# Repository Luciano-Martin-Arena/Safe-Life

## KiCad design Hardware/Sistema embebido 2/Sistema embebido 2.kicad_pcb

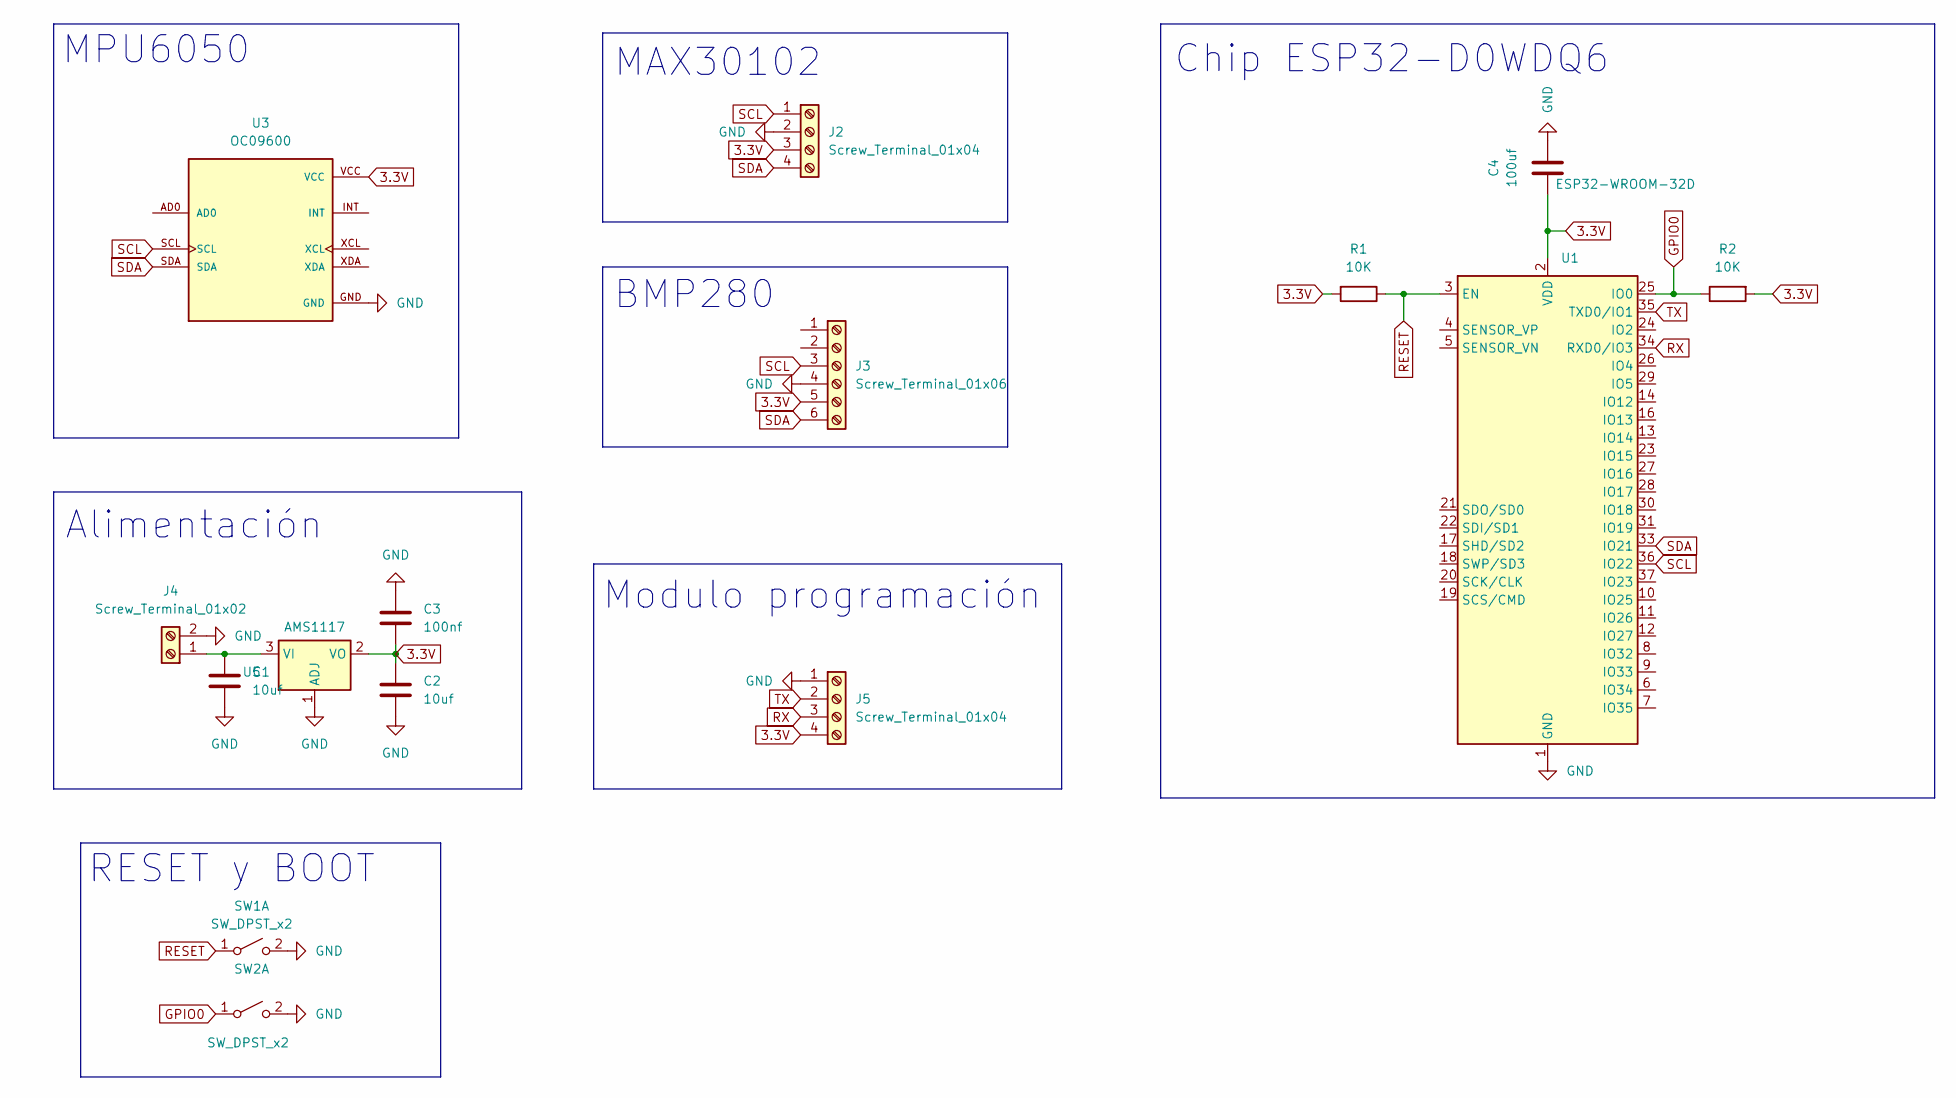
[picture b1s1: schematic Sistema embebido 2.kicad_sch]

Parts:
C1, C2: 10uf; C_0805_2012Metric_Pad1.18x1.45mm_HandSolder
C3: 100nf; C_0805_2012Metric_Pad1.18x1.45mm_HandSolder
C4: 100uf; C_0805_2012Metric_Pad1.18x1.45mm_HandSolder
J2, J5: Screw_Terminal_01x04; PinHeader_1x04_P2.54mm_Vertical
J3: Screw_Terminal_01x06; PinHeader_1x06_P2.54mm_Vertical
J4: Screw_Terminal_01x02; TerminalBlock_MaiXu_MX126-5.0-02P_1x02_P5.00mm
R1, R2: 10K; R_0805_2012Metric_Pad1.20x1.40mm_HandSolder
SW1, SW2: SW_DPST_x2; SW_SPST_B3U-1000P
U1: ESP32-WROOM-32D
U3: OC09600; MODULE_OC09600; PARTREV NA
U5: AMS1117; SOT-223-3_TabPin2

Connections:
3.3V: C2.1, C3.2, C4.1, J2.3, J3.5, J5.4, R1.2, R2.2, U1.2 (VDD), U3.VCC, U5.2 (VO)
GND: C1.2, C2.2, C3.1, C4.2, J2.2, J3.4, J4.2, J5.1, SW1.2 (B), SW2.2 (B), U1.1 (GND), U1.15 (GND), U1.38 (GND), U1.39 (GND), U3.GND, U5.1 (ADJ)
GPIO0: R2.1, SW2.1 (A), U1.25 (IO0)
unnamed: C1.1, J4.1, U5.3 (VI)
RESET: R1.1, SW1.1 (A), U1.3 (EN)
RX: J5.3, U1.34 (RXD0/IO3)
SCL: J2.1, J3.3, U1.36 (IO22), U3.SCL
SDA: J2.4, J3.6, U1.33 (IO21), U3.SDA
TX: J5.2, U1.35 (TXD0/IO1)

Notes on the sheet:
BMP280
RESET y BOOT
Alimentación
Modulo programación
MAX30102
MPU6050
Chip ESP32-D0WDQ6

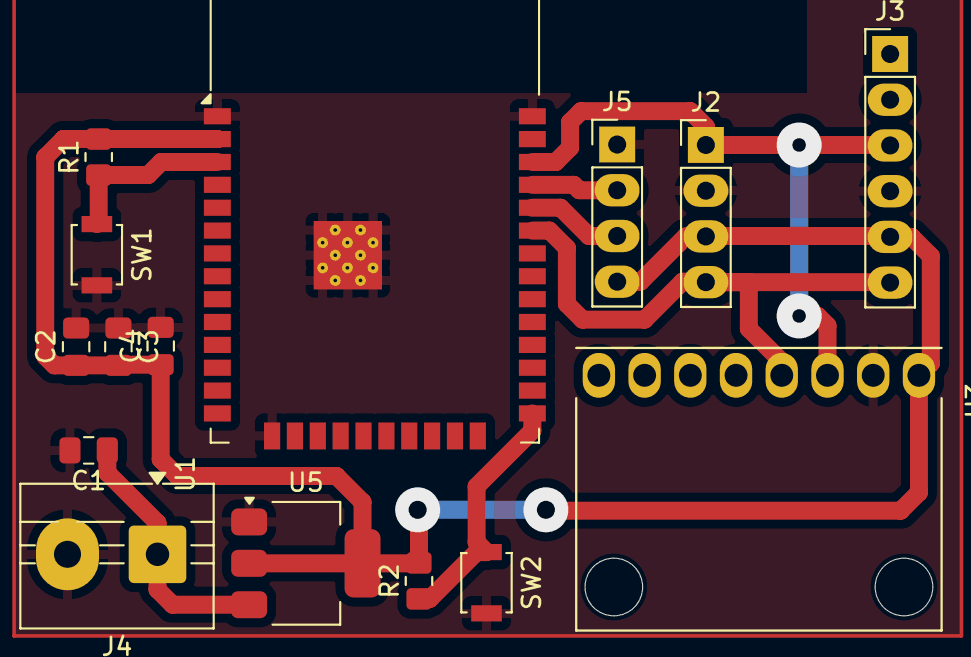
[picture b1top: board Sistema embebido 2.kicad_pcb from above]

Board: 2 copper layers, 15 parts (0 on the bottom side), 9 nets.

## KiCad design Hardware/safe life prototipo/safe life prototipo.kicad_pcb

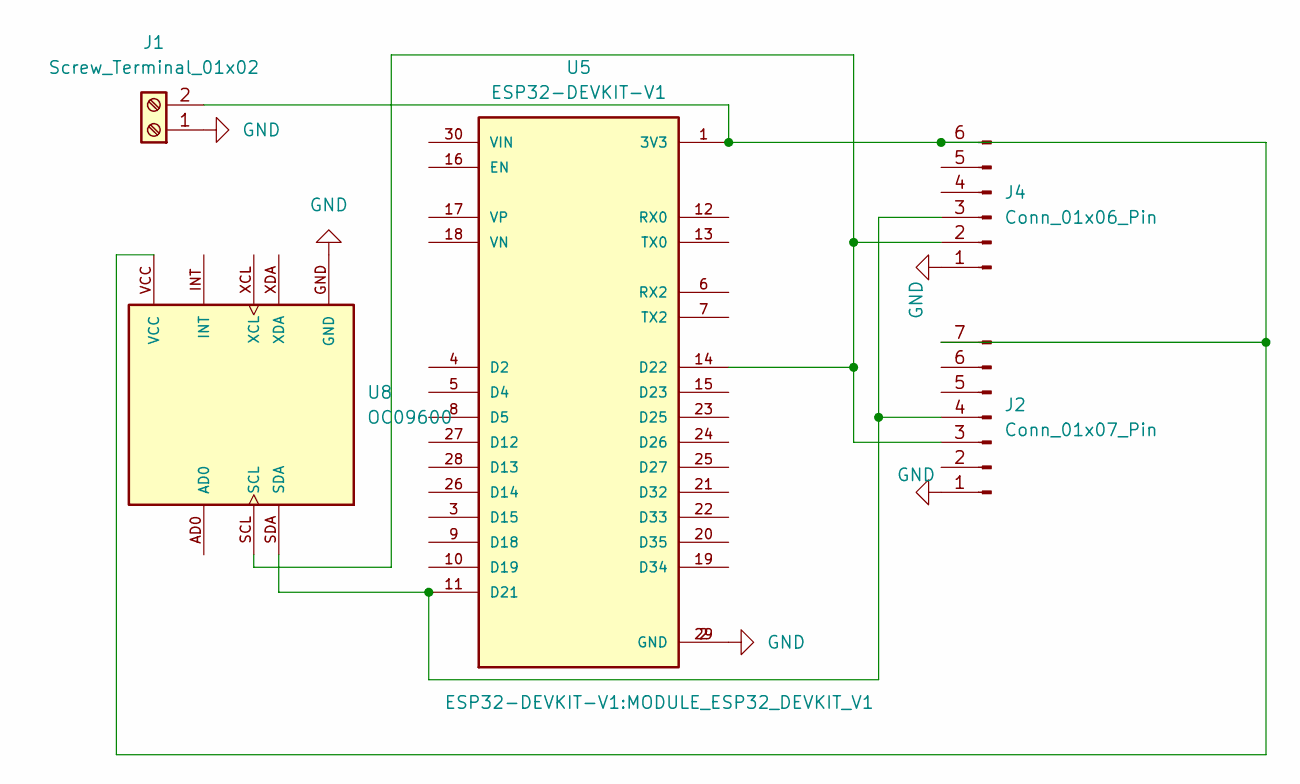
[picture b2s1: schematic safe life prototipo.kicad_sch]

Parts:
J1: Screw_Terminal_01x02; TerminalBlock_Xinya_XY308-2.54-2P_1x02_P2.54mm_Horizontal
J2: Conn_01x07_Pin; PinHeader_1x07_P2.54mm_Vertical
J4: Conn_01x06_Pin; PinHeader_1x06_P2.54mm_Vertical
U5: ESP32-DEVKIT-V1; MODULE_ESP32_DEVKIT_V1; PARTREV N/A
U8: OC09600; MODULE_OC09600; PARTREV NA

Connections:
GND: J1.1, J2.1, J4.1, U5.2 (GND), U5.29 (GND), U8.GND
unnamed: J1.2, J2.7, J4.6, U5.1 (3V3), U8.VCC
unnamed: J2.3, J4.2, U5.14 (D22), U8.SCL
unnamed: J2.4, J4.3, U5.11 (D21), U8.SDA

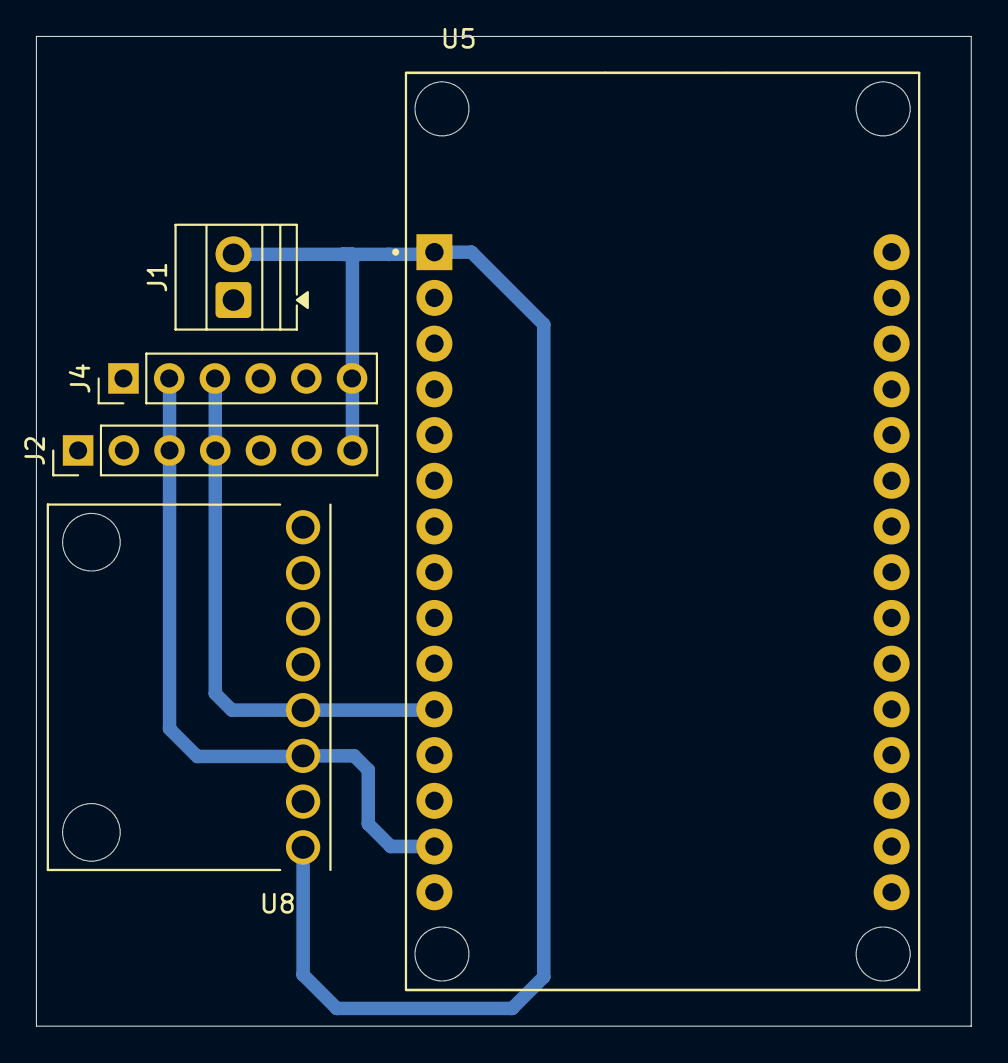
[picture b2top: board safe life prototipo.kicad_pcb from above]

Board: 2 copper layers, 51.9 x 55.0 mm, 5 parts (0 on the bottom side), 4 nets.

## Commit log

2026-06-25 Hardware
2026-06-25 Software
